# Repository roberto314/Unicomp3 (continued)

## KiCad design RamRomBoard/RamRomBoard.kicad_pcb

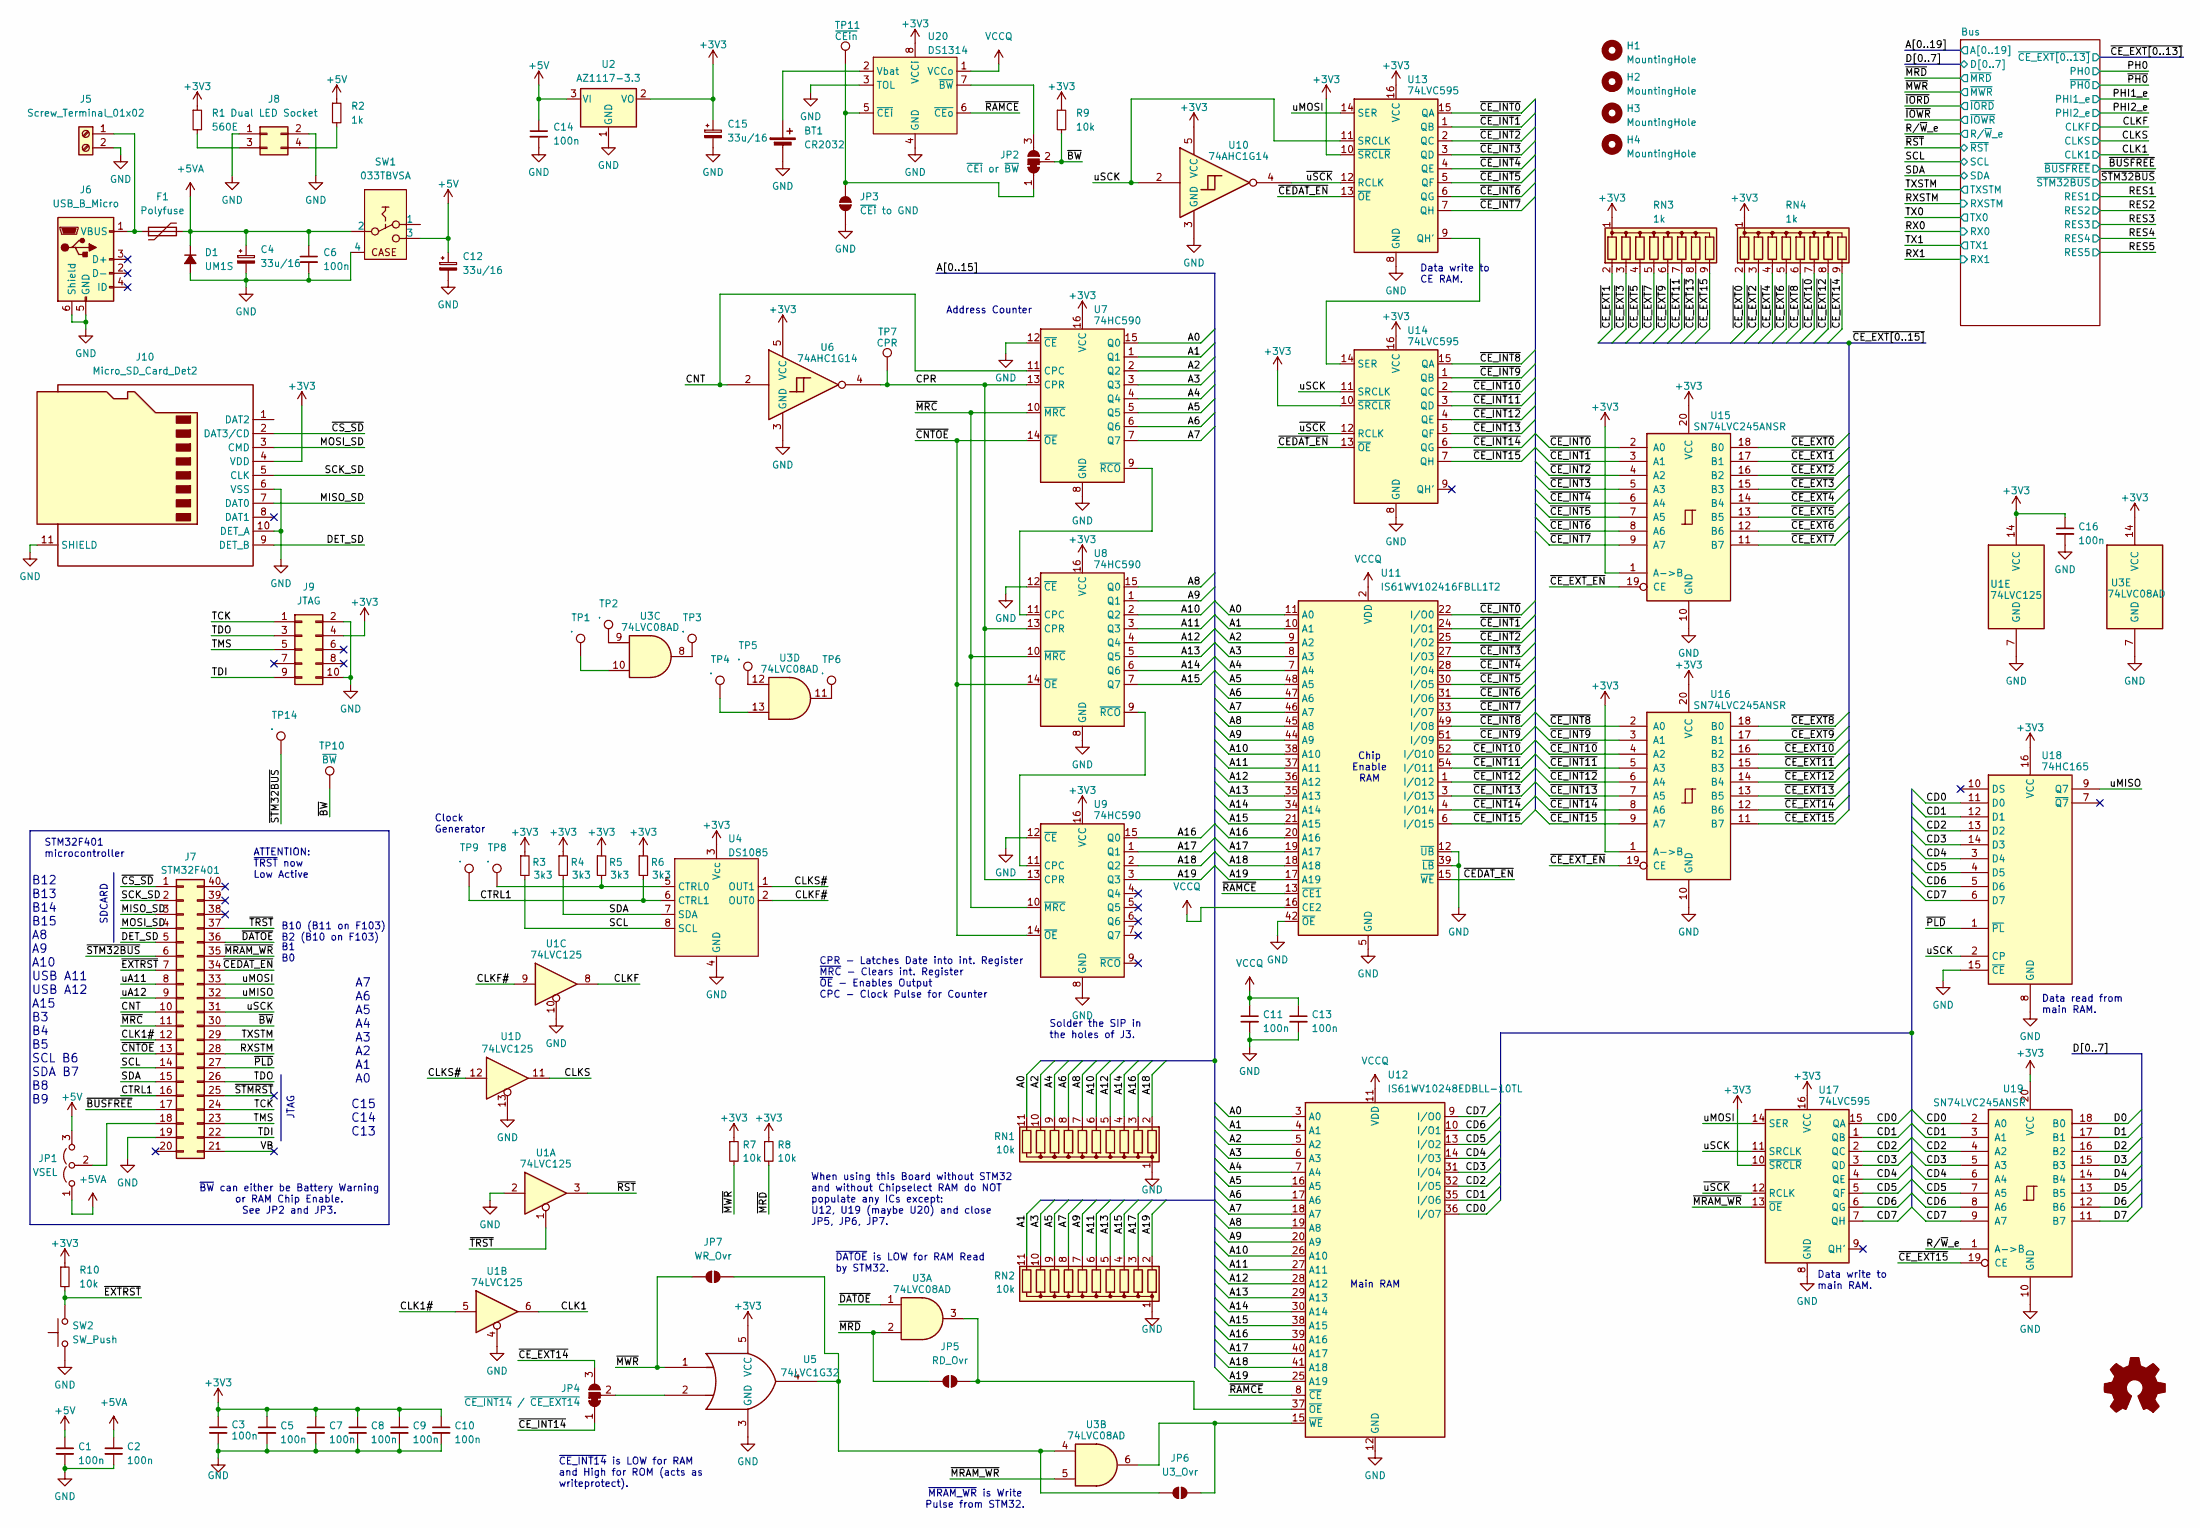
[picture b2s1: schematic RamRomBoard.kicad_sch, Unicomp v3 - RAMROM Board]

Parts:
BT1: CR2032; Battery_CR2032_Horizontal_ThreeHoles
C1, C2, C3, C5, C6, C7, C8, C9, C10, C11, C13, C14, C16: 100n; C_1206_3216Metric
C4, C12, C15: 33u/16; CP_EIA-7343-31_Kemet-D
D1: UM1S; D_SMB
F1: Polyfuse; Fuse_Littelfuse_395Series
H1, H2, H3, H4: MountingHole; MountingHole_3.2mm_M3
J5: Screw_Terminal_01x02; TerminalBlock_RND_205-00012_1x02_P5.00mm_Horizontal
J6: USB_B_Micro; USB_Micro-B_Amphenol_10104110_Horizontal
J7: STM32F401; DIP-40_W15.24mm_Socket_LongPads
J8: Dual LED Socket; PinHeader_2x02_P2.54mm_Vertical
J9: JTAG; PinHeader_2x05_P2.54mm_Horizontal
J10: Micro_SD_Card_Det2; microSD_HC_Hirose_DM3D-SF
JP1: VSEL; PinHeader_1x03_P2.54mm_Vertical
JP2: ~{CEi} or ~{BW}; SolderJumper-3_P1.3mm_Bridged12_RoundedPad1.0x1.5mm
JP3: ~{CEi} to GND; SolderJumper-2_P1.3mm_Open_RoundedPad1.0x1.5mm
JP4: ~{CE_INT14} / ~{CE_EXT14}; SolderJumper-3_P1.3mm_Bridged12_RoundedPad1.0x1.5mm
JP5: RD_Ovr; SolderJumper-2_P1.3mm_Open_RoundedPad1.0x1.5mm
JP6: U3_Ovr; SolderJumper-2_P1.3mm_Open_RoundedPad1.0x1.5mm
JP7: WR_Ovr; SolderJumper-2_P1.3mm_Open_RoundedPad1.0x1.5mm
R1: 560E; R_1206_3216Metric
R2: 1k; R_1206_3216Metric
R3, R4, R5, R6: 3k3; R_1206_3216Metric
R7, R8, R9, R10: 10k; R_1206_3216Metric
RN1, RN2: 10k; R_Array_SIP11
RN3, RN4: 1k; R_Array_SIP9
SW1: 033TBVSA; ToggleSwitch_CTS_033TBVS
SW2: SW_Push; SW_Tactile_SPST_Angled_PTS645Vx31-2LFS
TP1, TP2, TP3, TP4, TP5, TP6, TP8, TP9, TP14: .; PinHeader_1x01_P1.00mm_Vertical
TP7: CPR; PinHeader_1x01_P1.00mm_Vertical
TP10: ~{BW}; PinHeader_1x01_P1.00mm_Vertical
TP11: ~{CEin}; PinHeader_1x01_P1.00mm_Vertical
U1: 74LVC125; SOIC-14_3.9x8.7mm_P1.27mm
U2: AZ1117-3.3; SOT-223-3_TabPin2
U3: 74LVC08AD; SOIC-14_3.9x8.7mm_P1.27mm
U4: DS1085; SOIC-8_3.9x4.9mm_P1.27mm
U5: 74LVC1G32; SOT-23-5_HandSoldering
U6, U10: 74AHC1G14; SOT-23-5
U7, U8, U9: 74HC590; SOIC-16_3.9x9.9mm_P1.27mm
U11: IS61WV102416FBLL1T2; TSOP-II-54_22.2x10.16mm_P0.8mm
U12: IS61WV10248EDBLL-10TL; TSOP-II-44_10.16x18.41mm_P0.8mm
U13, U14, U17: 74LVC595; SO-16_3.9x9.9mm_P1.27mm
U15, U16, U19: SN74LVC245ANSR; SO-20_5.3x12.6mm_P1.27mm
U18: 74HC165; SOIC-16_3.9x9.9mm_P1.27mm
U20: DS1314; SOIC-8_3.9x4.9mm_P1.27mm

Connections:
+3V3: C3.1, C5.1, C7.1, C8.1, C9.1, C10.1, C15.1, C16.1, J9.4, J10.4 (VDD), R1.1, R3.1, R4.1, R5.1, R6.1, R7.1, R8.1, R9.1, R10.1, RN3.1 (common), RN4.1 (common), U1.14 (VCC), U2.2 (VO), U3.14 (VCC), U4.3 (Vcc), U5.5 (VCC), U6.5 (VCC), U7.16 (VCC), U8.16 (VCC), U9.16 (VCC), U10.5 (VCC), U13.10 (~SRCLR), U13.16 (VCC), U14.10 (~SRCLR), U14.16 (VCC), U15.1 (A->B), U15.20 (VCC), U16.1 (A->B), U16.20 (VCC), U17.10 (~SRCLR), U17.16 (VCC), U18.16 (VCC), U19.20 (VCC), U20.8 (VCCi); also elsewhere on the board
+5V: C1.1, C12.1, C14.1, JP1.3 (B), R2.1, SW1.3, U2.3 (VI); also elsewhere on the board
+5VA: C2.1, C4.1, C6.1, D1.1 (K), F1.2, JP1.1 (A), SW1.2; also elsewhere on the board
/A0: RN1.11 (R10), U7.15 (Q0), U11.11 (A0), U12.3 (A0); also elsewhere on the board
/A1: RN2.11 (R10), U7.1 (Q1), U11.10 (A1), U12.4 (A1); also elsewhere on the board
/A2: RN1.10 (R9), U7.2 (Q2), U11.9 (A2), U12.5 (A2); also elsewhere on the board
/A3: RN2.10 (R9), U7.3 (Q3), U11.8 (A3), U12.6 (A3); also elsewhere on the board
/A4: RN1.9 (R8), U7.4 (Q4), U11.7 (A4), U12.7 (A4); also elsewhere on the board
/A5: RN2.9 (R8), U7.5 (Q5), U11.48 (A5), U12.16 (A5); also elsewhere on the board
/A6: RN1.8 (R7), U7.6 (Q6), U11.47 (A6), U12.17 (A6); also elsewhere on the board
/A7: RN2.8 (R7), U7.7 (Q7), U11.46 (A7), U12.18 (A7); also elsewhere on the board
/A8: RN1.7 (R6), U8.15 (Q0), U11.45 (A8), U12.19 (A8); also elsewhere on the board
/A9: RN2.7 (R6), U8.1 (Q1), U11.44 (A9), U12.20 (A9); also elsewhere on the board
/A10: RN1.6 (R5), U8.2 (Q2), U11.38 (A10), U12.26 (A10); also elsewhere on the board
/A11: RN2.6 (R5), U8.3 (Q3), U11.37 (A11), U12.27 (A11); also elsewhere on the board
/A12: RN1.5 (R4), U8.4 (Q4), U11.36 (A12), U12.28 (A12); also elsewhere on the board
/A13: RN2.5 (R4), U8.5 (Q5), U11.35 (A13), U12.29 (A13); also elsewhere on the board
/A14: RN1.4 (R3), U8.6 (Q6), U11.34 (A14), U12.30 (A14); also elsewhere on the board
/A15: RN2.4 (R3), U8.7 (Q7), U11.21 (A15), U12.38 (A15); also elsewhere on the board
/A16: RN1.3 (R2), U9.15 (Q0), U11.20 (A16), U12.39 (A16); also elsewhere on the board
/A17: RN2.3 (R2), U9.1 (Q1), U11.19 (A17), U12.40 (A17); also elsewhere on the board
/A18: RN1.2 (R1), U9.2 (Q2), U11.18 (A18), U12.41 (A18); also elsewhere on the board
/A19: RN2.2 (R1), U9.3 (Q3), U11.17 (A19), U12.25 (A19); also elsewhere on the board
/CD0: U12.36 (I/O7), U17.15 (QA), U18.11 (D0), U19.2 (A0)
/CD1: U12.35 (I/O6), U17.1 (QB), U18.12 (D1), U19.3 (A1)
/CD2: U12.32 (I/O5), U17.2 (QC), U18.13 (D2), U19.4 (A2)
/CD3: U12.31 (I/O4), U17.3 (QD), U18.14 (D3), U19.5 (A3)
/CD4: U12.14 (I/O3), U17.4 (QE), U18.3 (D4), U19.6 (A4)
/CD5: U12.13 (I/O2), U17.5 (QF), U18.4 (D5), U19.7 (A5)
/CD6: U12.10 (I/O1), U17.6 (QG), U18.5 (D6), U19.8 (A6)
/CD7: U12.9 (I/O0), U17.7 (QH), U18.6 (D7), U19.9 (A7)
/CLK1: U1.6; also elsewhere on the board
/CLK1#: J7.12, U1.5
/CLKF: U1.8; also elsewhere on the board
/CLKF#: U1.9, U4.2 (OUT0)
/CLKS: U1.11; also elsewhere on the board
/CLKS#: U1.12, U4.1 (OUT1)
/CNT: J7.10, U6.2, U7.11 (CPC)
/CPR: TP7.1, U6.4, U7.13 (CPR), U8.13 (CPR), U9.13 (CPR)
/CTRL1: J7.16, R6.2, TP9.1, U4.6 (CTRL1)
/D0: U19.18 (B0); also elsewhere on the board
/D1: U19.17 (B1); also elsewhere on the board
/D2: U19.16 (B2); also elsewhere on the board
/D3: U19.15 (B3); also elsewhere on the board
/D4: U19.14 (B4); also elsewhere on the board
/D5: U19.13 (B5); also elsewhere on the board
/D6: U19.12 (B6); also elsewhere on the board
/D7: U19.11 (B7); also elsewhere on the board
/DET_SD: J7.5, J10.9 (DET_B)
/MISO_SD: J7.3, J10.7 (DAT0)
/MOSI_SD: J7.4, J10.3 (CMD)
/RXSTM: J7.28; also elsewhere on the board
/R/~W_e: U19.1 (A->B); also elsewhere on the board
/SCK_SD: J7.2, J10.5 (CLK)
/SCL: J7.14, R3.2, U4.8 (SCL); also elsewhere on the board
/SDA: J7.15, R4.2, U4.7 (SDA); also elsewhere on the board
/TCK: J7.24, J9.1
/TDI: J7.22, J9.9
/TDO: J7.26, J9.3
/TMS: J7.23, J9.5
/TXSTM: J7.29; also elsewhere on the board
/VB: J7.21
/uA11: J7.8
/uA12: J7.9
/uMISO: J7.32, U18.9 (Q7)
/uMOSI: J7.33, U13.14 (SER), U17.14 (SER)
/uSCK: J7.31, U10.2, U13.11 (SRCLK), U14.11 (SRCLK), U17.11 (SRCLK), U18.2 (CP)
/~BUSFREE: J7.17; also elsewhere on the board
/~BW: J7.30, JP2.2 (C), R9.2, TP10.1
/~CEDAT_EN: J7.34, U11.15 (~WE), U13.13 (~OE), U14.13 (~OE)
/~CE_EXT0: RN4.2 (R1), U15.18 (B0); also elsewhere on the board
/~CE_EXT1: RN3.2 (R1), U15.17 (B1); also elsewhere on the board
/~CE_EXT2: RN4.3 (R2), U15.16 (B2); also elsewhere on the board
/~CE_EXT3: RN3.3 (R2), U15.15 (B3); also elsewhere on the board
/~CE_EXT4: RN4.4 (R3), U15.14 (B4); also elsewhere on the board
/~CE_EXT5: RN3.4 (R3), U15.13 (B5); also elsewhere on the board
/~CE_EXT6: RN4.5 (R4), U15.12 (B6); also elsewhere on the board
/~CE_EXT7: RN3.5 (R4), U15.11 (B7); also elsewhere on the board
/~CE_EXT8: RN4.6 (R5), U16.18 (B0); also elsewhere on the board
/~CE_EXT9: RN3.6 (R5), U16.17 (B1); also elsewhere on the board
/~CE_EXT10: RN4.7 (R6), U16.16 (B2); also elsewhere on the board
/~CE_EXT11: RN3.7 (R6), U16.15 (B3); also elsewhere on the board
/~CE_EXT12: RN4.8 (R7), U16.14 (B4); also elsewhere on the board
/~CE_EXT13: RN3.8 (R7), U16.13 (B5); also elsewhere on the board
/~CE_EXT14: JP4.3 (B), RN4.9 (R8), U16.12 (B6)
/~CE_EXT15: RN3.9 (R8), U16.11 (B7), U19.19 (CE)
/~CE_EXT_EN: U15.19 (CE), U16.19 (CE)
/~CE_INT0: U11.22 (I/O0), U13.15 (QA), U15.2 (A0)
/~CE_INT1: U11.24 (I/O1), U13.1 (QB), U15.3 (A1)
/~CE_INT2: U11.25 (I/O2), U13.2 (QC), U15.4 (A2)
/~CE_INT3: U11.27 (I/O3), U13.3 (QD), U15.5 (A3)
/~CE_INT4: U11.28 (I/O4), U13.4 (QE), U15.6 (A4)
/~CE_INT5: U11.30 (I/O5), U13.5 (QF), U15.7 (A5)
/~CE_INT6: U11.31 (I/O6), U13.6 (QG), U15.8 (A6)
/~CE_INT7: U11.33 (I/O7), U13.7 (QH), U15.9 (A7)
/~CE_INT8: U11.49 (I/O8), U14.15 (QA), U16.2 (A0)
/~CE_INT9: U11.51 (I/O9), U14.1 (QB), U16.3 (A1)
/~CE_INT10: U11.52 (I/O10), U14.2 (QC), U16.4 (A2)
/~CE_INT11: U11.54 (I/O11), U14.3 (QD), U16.5 (A3)
/~CE_INT12: U11.1 (I/O12), U14.4 (QE), U16.6 (A4)
/~CE_INT13: U11.3 (I/O13), U14.5 (QF), U16.7 (A5)
/~CE_INT14: JP4.1 (A), U11.4 (I/O14), U14.6 (QG), U16.8 (A6)
/~CE_INT15: U11.6 (I/O15), U14.7 (QH), U16.9 (A7)
/~CNTOE: J7.13, U7.14 (~OE), U8.14 (~OE), U9.14 (~OE)
/~CS_SD: J7.1, J10.2 (DAT3/CD)
/~DATOE: J7.36, U3.1
/~EXTRST: J7.7, R10.2, SW2.2
/~MRAM_WR: J7.35, U3.5, U17.13 (~OE)
/~MRC: J7.11, U7.10 (~MRC), U8.10 (~MRC), U9.10 (~MRC)
/~MRD: JP5.2 (B), R8.2, U3.2; also elsewhere on the board
/~MWR: JP7.2 (B), R7.2, U5.1; also elsewhere on the board
/~PLD: J7.27, U18.1 (~PL)
/~RAMCE: U11.13 (~CE1), U12.8 (~CE), U20.6 (~CEo)
/~RST: U1.3; also elsewhere on the board
/~STM32BUS: J7.6, TP14.1; also elsewhere on the board
/~STMRST: J7.25
/~TRST: J7.37, U1.1
/~uSCK: U10.4, U13.12 (RCLK), U14.12 (RCLK), U17.12 (RCLK)
GND: BT1.2 (-), C1.2, C2.2, C3.2, C4.2, C5.2, C6.2, C7.2, C8.2, C9.2, C10.2, C11.2, C12.2, C13.2, C14.2, C15.2, C16.2, D1.2 (A), J5.2, J6.5 (GND), J6.6 (Shield), J7.19, J8.1, J8.2, J9.2, J9.10, J10.6 (VSS), J10.10 (DET_A), J10.11 (SHIELD), JP3.1 (A), RN1.1 (common), RN2.1 (common), SW1.4, SW2.1, U1.2, U1.4, U1.7 (GND), U1.10, U1.13, U2.1 (GND), U3.7 (GND), U4.4 (GND), U5.3 (GND), U6.3 (GND), U7.8 (GND), U7.12 (~CE), U8.8 (GND), U8.12 (~CE), U9.8 (GND), U9.12 (~CE), U10.3 (GND), U11.5 (GND), U11.12 (~UB), U11.26 (GND), U11.32 (GND), U11.39 (~LB), U11.41 (GND), U11.42 (~OE), U11.53 (GND), U12.12 (GND), U12.34 (GND), U13.8 (GND), U14.8 (GND), U15.10 (GND), U16.10 (GND), U17.8 (GND), U18.8 (GND), U18.15 (~CE), U19.10 (GND), U20.3 (TOL), U20.4 (GND); also elsewhere on the board
unnamed: BT1.1 (+), U20.2 (Vbat)
unnamed: F1.1, J5.1, J6.1 (VBUS)
unnamed: J7.18, JP1.2 (C)
unnamed: J8.3, R1.2
unnamed: J8.4, R2.2
unnamed: JP2.1 (A), JP3.2 (B), TP11.1, U20.5 (~CEi)
unnamed: JP2.3 (B), U20.7 (~BW)
unnamed: JP4.2 (C), U5.2
unnamed: JP5.1 (A), U3.3, U12.37 (~OE)
unnamed: JP6.1 (A), U3.6, U12.15 (~WE)
unnamed: JP6.2 (B), JP7.1 (A), U3.4, U5.4
unnamed: TP1.1, U3.10
unnamed: TP2.1, U3.9
unnamed: TP3.1, U3.8
unnamed: TP4.1, U3.13
unnamed: TP5.1, U3.12
unnamed: TP6.1, U3.11
unnamed: R5.2, TP8.1, U4.5 (CTRL0)
unnamed: U7.9 (~RCO), U8.11 (CPC)
unnamed: U8.9 (~RCO), U9.11 (CPC)
unnamed: U13.9 (QH'), U14.14 (SER)
VCCQ: C11.1, C13.1, U11.2 (VDD), U11.14 (VDD), U11.16 (CE2), U11.23 (VDD), U11.29 (VDD), U11.50 (VDD), U12.11 (VDD), U12.33 (VDD), U20.1 (VCCo)

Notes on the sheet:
SDCARD
B1 B0
When using this Board without STM32 and without Chipselect RAM do NOT populate any ICs except: U12, U19 (maybe U20) and close JP5, JP6, JP7.
Data write to main RAM.
JTAG
ATTENTION: ~{TRST} now Low Active
CPR - Latches Date into int. Register ~{MRC} - Clears int. Register ~{OE} - Enables Output CPC - Clock Pulse for Counter
~{CE_INT14} is LOW for RAM and High for ROM (acts as writeprotect).
Data write to CE RAM.
~{BW} can either be Battery Warning or RAM Chip Enable. See JP2 and JP3.
B10 (B11 on F103) B2 (B10 on F103)
Chip Enable RAM
~{DATOE} is LOW for RAM Read by STM32.
A7 A6 A5 A4 A3 A2 A1 A0
Clock Generator
~{MRAM_WR} is Write Pulse from STM32.
Solder the SIP in the holes of J3.
B12 B13 B14 B15 A8 A9 A10 USB A11 USB A12 A15 B3 B4 B5 SCL B6 SDA B7 B8 B9
Main RAM
C15 C14 C13
Data read from main RAM.
STM32F401 microcontroller
Address Counter

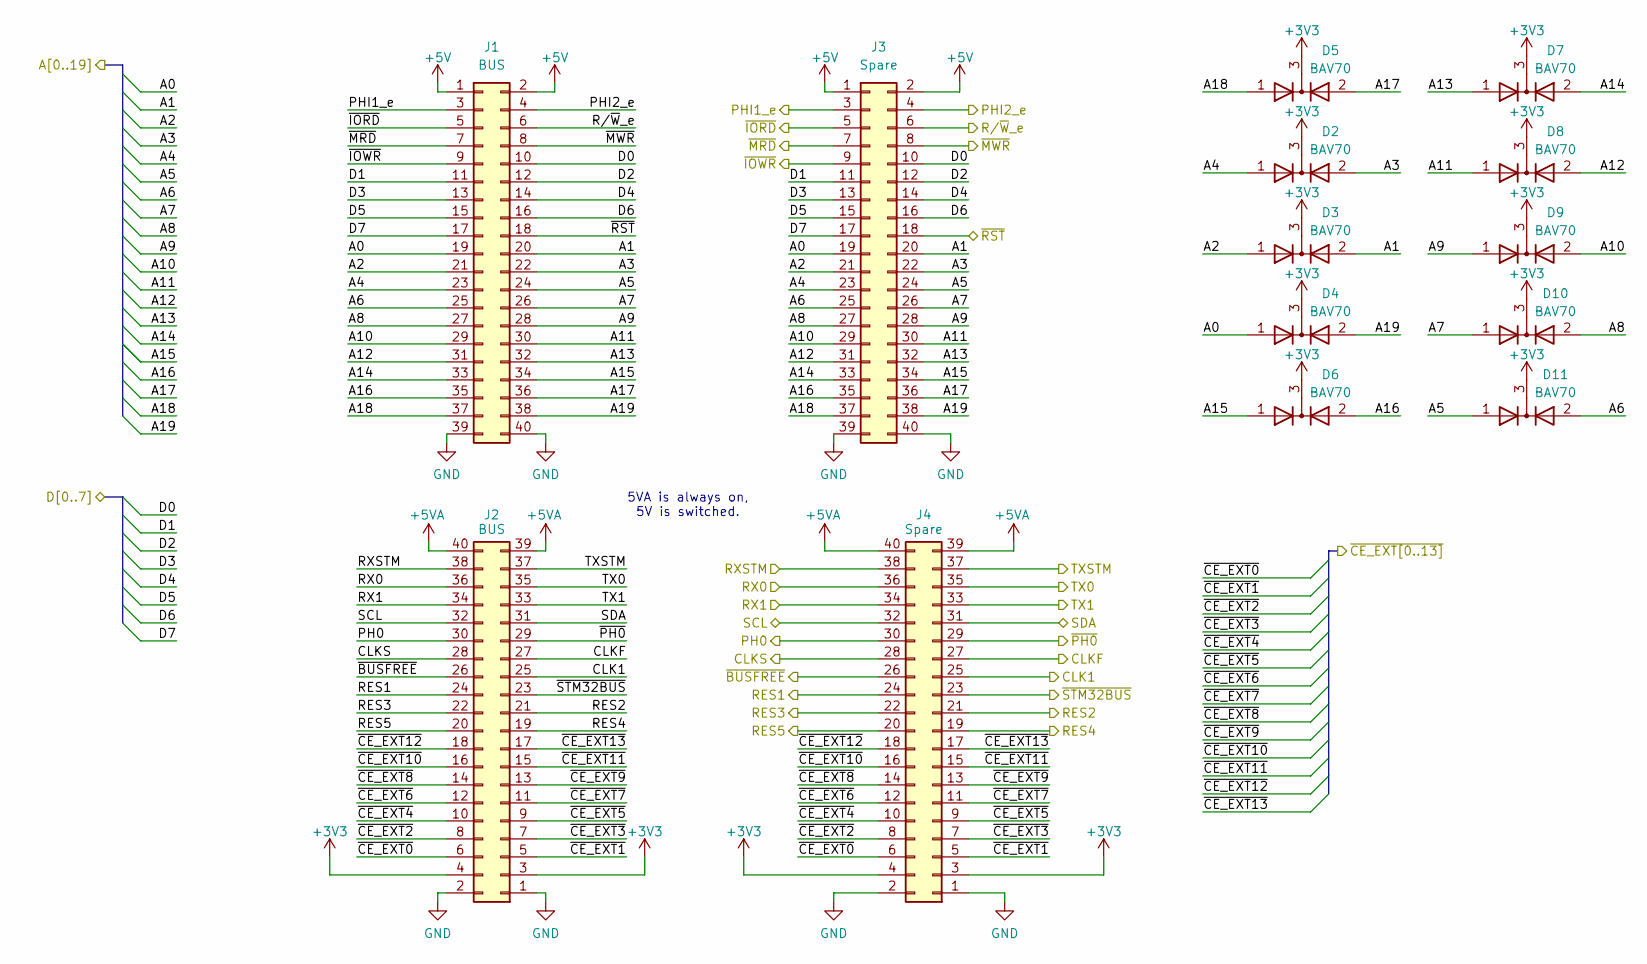
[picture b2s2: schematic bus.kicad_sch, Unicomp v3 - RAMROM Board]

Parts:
D2, D3, D4, D5, D6, D7, D8, D9, D10, D11: BAV70; SOT-23
J1, J2: BUS; PinSocket_2x20_P2.54mm_Vertical
J3, J4: Spare; PinSocket_2x20_P2.54mm_Vertical

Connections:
+3V3: D2.3 (K), D3.3 (K), D4.3 (K), D5.3 (K), D6.3 (K), D7.3 (K), D8.3 (K), D9.3 (K), D10.3 (K), D11.3 (K), J2.3, J2.4, J4.3, J4.4; also elsewhere on the board
+5V: J1.1, J1.2, J3.1, J3.2; also elsewhere on the board
+5VA: J2.39, J2.40, J4.39, J4.40; also elsewhere on the board
/A0: D4.1 (A), J1.19, J3.19; also elsewhere on the board
/A1: D3.2 (A), J1.20, J3.20; also elsewhere on the board
/A2: D3.1 (A), J1.21, J3.21; also elsewhere on the board
/A3: D2.2 (A), J1.22, J3.22; also elsewhere on the board
/A4: D2.1 (A), J1.23, J3.23; also elsewhere on the board
/A5: D11.1 (A), J1.24, J3.24; also elsewhere on the board
/A6: D11.2 (A), J1.25, J3.25; also elsewhere on the board
/A7: D10.1 (A), J1.26, J3.26; also elsewhere on the board
/A8: D10.2 (A), J1.27, J3.27; also elsewhere on the board
/A9: D9.1 (A), J1.28, J3.28; also elsewhere on the board
/A10: D9.2 (A), J1.29, J3.29; also elsewhere on the board
/A11: D8.1 (A), J1.30, J3.30; also elsewhere on the board
/A12: D8.2 (A), J1.31, J3.31; also elsewhere on the board
/A13: D7.1 (A), J1.32, J3.32; also elsewhere on the board
/A14: D7.2 (A), J1.33, J3.33; also elsewhere on the board
/A15: D6.1 (A), J1.34, J3.34; also elsewhere on the board
/A16: D6.2 (A), J1.35, J3.35; also elsewhere on the board
/A17: D5.2 (A), J1.36, J3.36; also elsewhere on the board
/A18: D5.1 (A), J1.37, J3.37; also elsewhere on the board
/A19: D4.2 (A), J1.38, J3.38; also elsewhere on the board
/CLK1: J2.25, J4.25; also elsewhere on the board
/CLKF: J2.27, J4.27; also elsewhere on the board
/CLKS: J2.28, J4.28; also elsewhere on the board
/D0: J1.10, J3.10; also elsewhere on the board
/D1: J1.11, J3.11; also elsewhere on the board
/D2: J1.12, J3.12; also elsewhere on the board
/D3: J1.13, J3.13; also elsewhere on the board
/D4: J1.14, J3.14; also elsewhere on the board
/D5: J1.15, J3.15; also elsewhere on the board
/D6: J1.16, J3.16; also elsewhere on the board
/D7: J1.17, J3.17; also elsewhere on the board
/PH0: J2.30, J4.30
/PHI1_e: J1.3, J3.3
/PHI2_e: J1.4, J3.4
/RES1: J2.24, J4.24
/RES2: J2.21, J4.21
/RES3: J2.22, J4.22
/RES4: J2.19, J4.19
/RES5: J2.20, J4.20
/RX0: J2.36, J4.36
/RX1: J2.34, J4.34
/RXSTM: J2.38, J4.38; also elsewhere on the board
/R/~W_e: J1.6, J3.6; also elsewhere on the board
/SCL: J2.32, J4.32; also elsewhere on the board
/SDA: J2.31, J4.31; also elsewhere on the board
/TX0: J2.35, J4.35
/TX1: J2.33, J4.33
/TXSTM: J2.37, J4.37; also elsewhere on the board
/~BUSFREE: J2.26, J4.26; also elsewhere on the board
/~CE_EXT0: J2.6, J4.6; also elsewhere on the board
/~CE_EXT1: J2.5, J4.5; also elsewhere on the board
/~CE_EXT2: J2.8, J4.8; also elsewhere on the board
/~CE_EXT3: J2.7, J4.7; also elsewhere on the board
/~CE_EXT4: J2.10, J4.10; also elsewhere on the board
/~CE_EXT5: J2.9, J4.9; also elsewhere on the board
/~CE_EXT6: J2.12, J4.12; also elsewhere on the board
/~CE_EXT7: J2.11, J4.11; also elsewhere on the board
/~CE_EXT8: J2.14, J4.14; also elsewhere on the board
/~CE_EXT9: J2.13, J4.13; also elsewhere on the board
/~CE_EXT10: J2.16, J4.16; also elsewhere on the board
/~CE_EXT11: J2.15, J4.15; also elsewhere on the board
/~CE_EXT12: J2.18, J4.18; also elsewhere on the board
/~CE_EXT13: J2.17, J4.17; also elsewhere on the board
/~IORD: J1.5, J3.5
/~IOWR: J1.9, J3.9
/~MRD: J1.7, J3.7; also elsewhere on the board
/~MWR: J1.8, J3.8; also elsewhere on the board
/~PH0: J2.29, J4.29
/~RST: J1.18, J3.18; also elsewhere on the board
/~STM32BUS: J2.23, J4.23; also elsewhere on the board
GND: J1.39, J1.40, J2.1, J2.2, J3.39, J3.40, J4.1, J4.2; also elsewhere on the board

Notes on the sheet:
5VA is always on, 5V is switched.

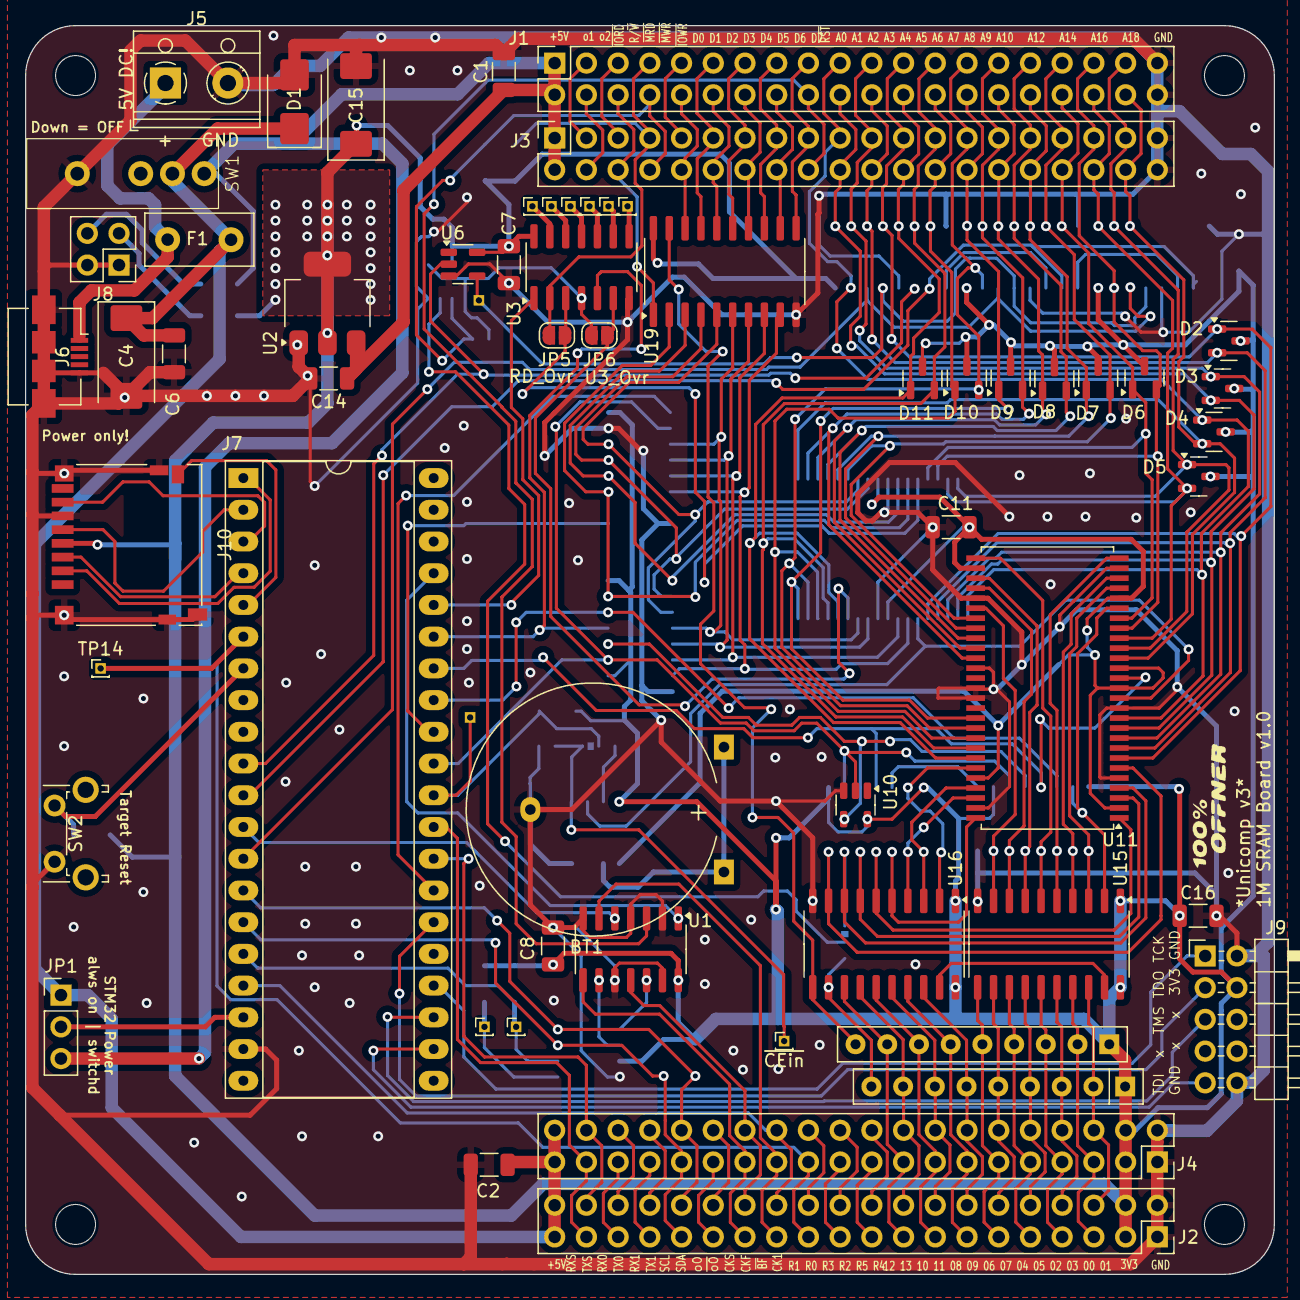
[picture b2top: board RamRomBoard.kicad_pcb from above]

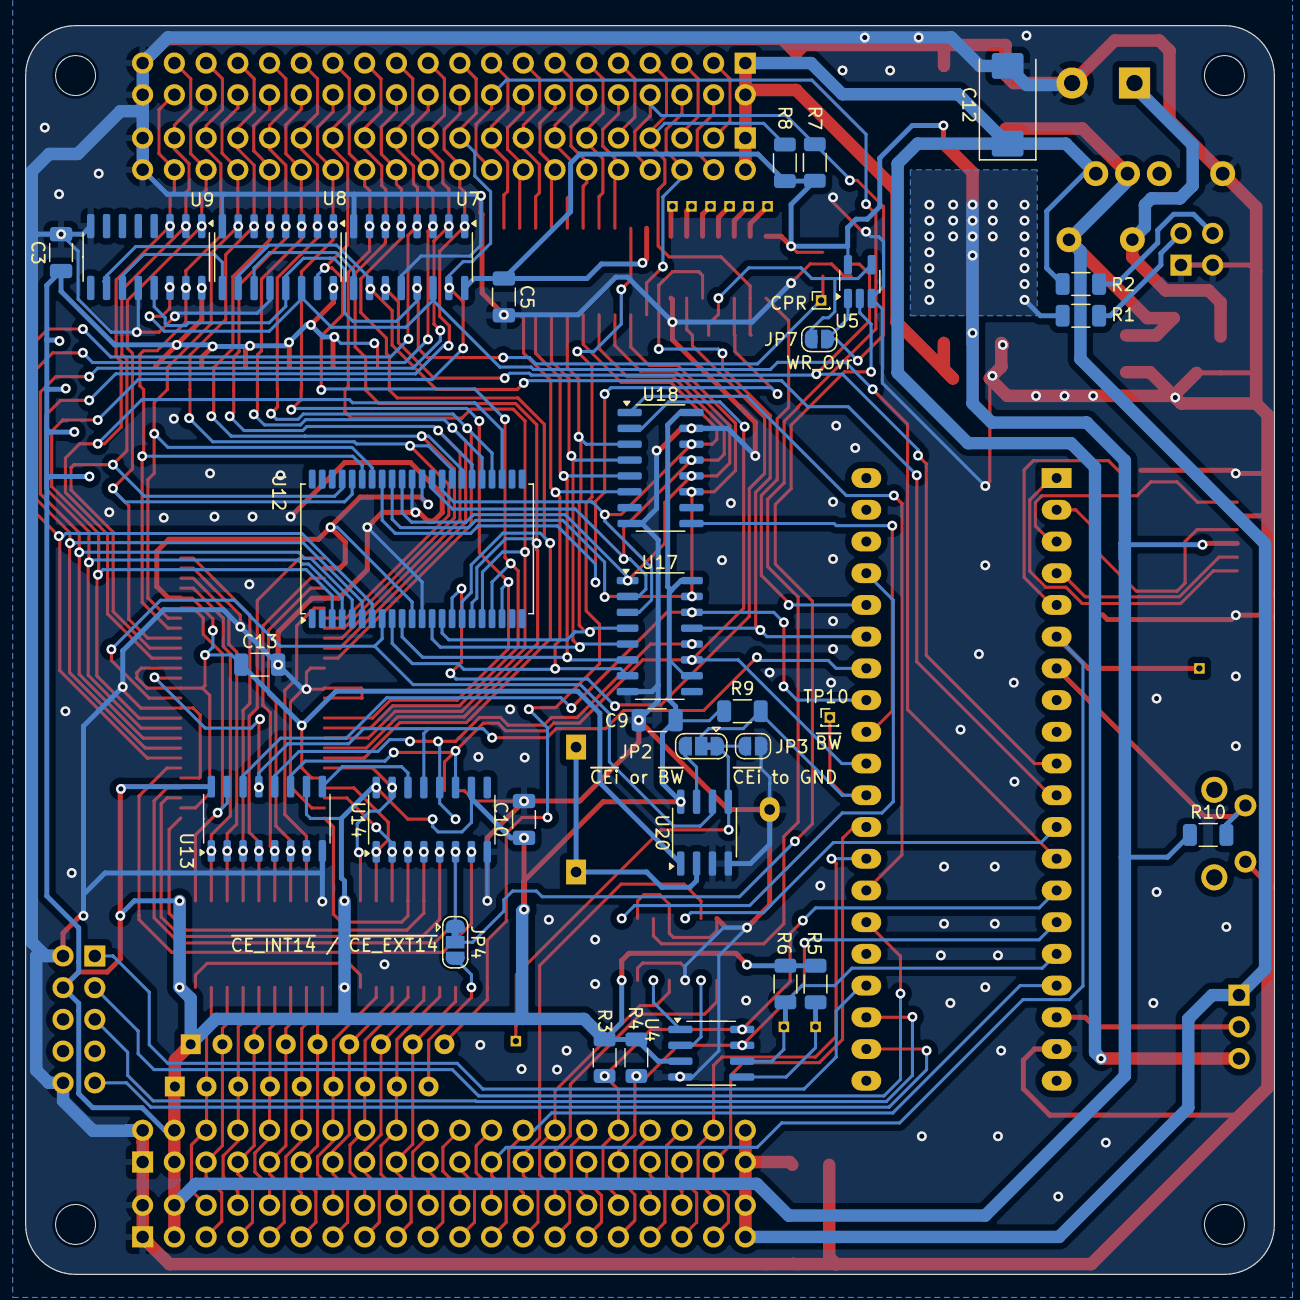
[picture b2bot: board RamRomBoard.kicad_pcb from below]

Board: 2 copper layers, 100.0 x 100.0 mm, 96 parts (33 on the bottom side), 152 nets.
